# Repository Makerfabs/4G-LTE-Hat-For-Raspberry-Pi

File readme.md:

# 4G LTE Hat For Raspberry Pi

```c++
/*
Version:		V1.0
Author:			Vincent
Create Date:	2022/2/24
Note:
	
*/
```

[toc]

# Makerfabs

[Makerfabs home page](https://www.makerfabs.com/)

[Makerfabs Wiki](https://wiki.makerfabs.com/)

# 4G LTE Hat For Raspberry Pi
## Intruduce

Product Link ：[4G LTE Hat For Raspberry Pi(SIM7600X)]() 

Wiki Link : [4G LTE Hat For Raspberry Pi]() 

4G LTE Hat For Raspberry Pi integrated two types of the 4G LTE CAT4 module SIM7600A-H or SIM7600E-H, SIM7600A-H/SIM7600E-H is a complete multi-band LTE-FDD/LTE-TDD/HSPA+/UMTS/EDGE/GPRS/GSM module solution in LCC type which supports LTE CAT4 up to 150Mbps for downlink and 50Mbps for uplink data transfer, much faster and popular than 2G/3G.

It can be used as a wireless card with USB and raspberry PI connections. It can also be controlled through GPIO's hardware UART.

## Module Type

## Feature

- Supports dial-up, phone, SMS, TCP, UDP, DTMF, HTTP, FTP, and so on
- USB Type C port
- Control Via AT Commands
- Board USB supply voltage range: 4.8~5.5V, 5.0V Typical
- 3GPP E-UTRA Release 11
- IPEX Antenna, GSM/UMTS/LTE main antenna. UMTS/LTE auxiliary antenna. GNSS antenna
- SMS support
- Audio support
- Audio chip: NAU8810
- Level Shifter: TXS0108E

### Front:

### Back:

### Frequency bands

### Transfer Speed

## AT Command Explain

###  AT commands test

Refer to the official AT manual of SIM7600 for detailed return values.

```c++
    AT+CGMI    // Request manufacturer identification
    AT+CGMM    // Request model identification
    AT+CGSN    // Request product serial number identification
    AT+CSUB    // Request the module version and chip
    AT+CPIN?     // Request the state of the SIM card
    AT+CICCID    // Read ICCID from SIM card
    AT+CNUM      // Request the subscriber number
    AT+CNMP?     // Preferred mode selection
    AT+COPS?     // Check the current network operator
```

### Get the GNSS location

GPS signal acquisition speed depends on signal strength, please wait patiently in an open place.

```c++
    AT+CGPS=1      // Start GPS session 
    AT+CGPSINFO    // Get GPS fixed position information
    AT+CGPS=0      // Stop GPS session
```

### Send and receive SMS

Please consult the operator for the phone number of the SMS center. The number "+8613800755500" in Shenzhen was used in the test. 

```c++
    AT+CSCA="XXXXXX"       // Set the SMS service centre address
    AT+CMGF=1              // Select SMS message format
    AT+CMGS="xxxxxx"       // Send message to "xxxxxx"(the receiver number).
```

"AT+CMGS" sets the phone number of the receiver and returns ' >' . Send desired content, such as "Send Massage Test!".After editing a short message, send it in hexadecimal format 1A Send a message.

*The Arduino IDE cannot send hexadecimal,  you can use other software. In the example code, entering 1A or 1A will send 0x1A to the module.*

# Usage (Pi with USB)

## Equipment list

- Maduino Zero 4G (With GPS antenna and two 4G-GSM antennas)
- SIM card 

*Ensure that SIM7600 requirements are met and that the system can communicate with local carriers. We used China Mobile's 4G card for testing.*

- Connect all antennas
- Insert a SIM card
- Connect **USB for MCU** to Raspberry Pi USB

## Used as a 4G network adapter

### Hardware Check

- Log in to the root account and perform all subsequent operations as the root account.

```shell
sudo su
```

- Install the Minicom serial port tool.

```shell
apt-get install minicom
```

- To view the serial port device, AT command serial port: "/dev/ttyUSB2"

```shell
ls /dev/ttyUSB*
```

- Open the serial port with Minicom

```shell
minicom -D /dev/ttyUSB2
```

- Enter the AT command in minicom

```shell
# Forcibly set the Internet access to 4G
AT+CNMP=38
# Querying network Quality
AT+CSQ
# Query the network registry
AT+CREG?
# Querying Network Carrier Information
AT+COPS?
# Querying network band
AT+CPSI?
```

- \- Press Ctrl + A, then X to exit Minicom

At this point, the hardware and network connections between SIM7600CE and Raspberry Pi are normal. This case uses the 4G card of China Mobile. If you cannot use the other areas, please ask SIMCOM. 

### Driver Install

By default, Raspbian is installed with Qualcomm driver files for the wwan0 network port. For Raspberry Pi, you need to uninstall the driver first (otherwise it will conflict with the new driver), and then install the Simcom's driver for wwan0.

- Check system drivers

```shell
lsmod
```

- Uninstalling an existing driver

```shell
rmmod qmi_wwan
```

- Install the raspberry PI kernel header file
```shell
apt install raspberrypi-kernel-headers
```
- Download the official driver program provided by SIMCOM
```shell
wget https://www.waveshare.net/w/upload/0/00/SIM7600_NDIS.7z
```
- Install the decompression tool and decompress it
```shell
apt-get install p7zip-full
7z x SIM7600_NDIS.7z -r -o ./SIM7600_NDIS
```
- Go to the driver folder and compile

```shell
cd SIM7600_NDIS
make clean
make
ls
```

- Install the driver module file

```shell
insmod simcom_wwan.ko
```

- Check whether the installation is successful
```shell
lsmod
```

### Assign IP addresses

- In this case, the wwan0 network port is displayed

```shell
ifconfig -a
```
- However, no IP address is assigned to the network port. To assign an IP address, enable the network port first

```shell
ifconfig wwan0 up
```
- Then, through Minicom, enter the AT command to start dialing

```shell
minicom -D /dev/ttyUSB2
AT$QCRMCALL=1,1
```
- Finally, exit Minicom and assign IP

```shell
apt-get install udhcpc
udhcpc -i wwan0
```
- Run the Ping command to check whether the network adapter is connected

```shell
ping -I wwan0 www.baidu.com
```

# Usage (Pi with Uart)

We have connected the UART pin of SIM7600 to the UART of raspberry PI via GPIO.

SIM7600 can be connected using PySerial and other libraries. However, you need to set up the raspberry PI hardware UART, and it will use the Raspberry PI bluetooth.

The setting method is as follows:

```shell
#Set Pi uart
sudo raspi-config 

#Select interface options
#Select Serial Port
#Turn off serial login shell
#Open serial hardware
#Finish and reboot

#Install serial library
sudo apt-get update
sudo apt-get install pip
sudo pip install pyserial

python test.py
#Code is below
#Entry some at commands
```

**test.py**：

```python
import serial
from time import sleep
ser = serial.Serial("/dev/ttyS0", 115200)  # Open port with baud rate
while True:
    # Read cmd
    # You need press enter to receive new message
    # input() is block function
    cmd_input = input()
    if cmd_input != "":
        ser.write((cmd_input + "\r\n").encode('gbk'))

    # ser.write("AT".encode())  # It's error
    # ser.write("AT\r\n".encode('utf-8'))  # It's correct, contain "\r\n"
    sleep(1)

    # Receieve from SIM7600
    received_data = ser.read_all()  # read serial port
    print(received_data)  # print received bytes
    if received_data.decode() != "":
        print("Back:" + received_data.decode())  # print received data after decode

```

The AT-Command used are no different from those under Minicom.

**You need to manually add "\r\n", otherwise the module will just repeat the instructions you sent. **

# Usage （Windows）

- Connect one end of USB cable to USB interface of PC and the other end to USB_LTE interface of Maduino Zero 4G LTE.

- Open the device manager and you can see these COM ports.

- If the COM port is identified in the figure above, but an exclamation mark appears, it indicates that the driver is not installed.
- Driver is in "Maduino-Zero-4G-LTE\win_driver\SIM7600X-Driver.7z"
- Open Device Manager - > Other equipment - >“SimTech,Incorporated”- >  Update the driver - > Browse my computer to find driver files - > Select a path for saving the driver file based on the system- >The installation is complete.

- Install the driver for each exclamation point
- The network icon will then appear as a cellular network.

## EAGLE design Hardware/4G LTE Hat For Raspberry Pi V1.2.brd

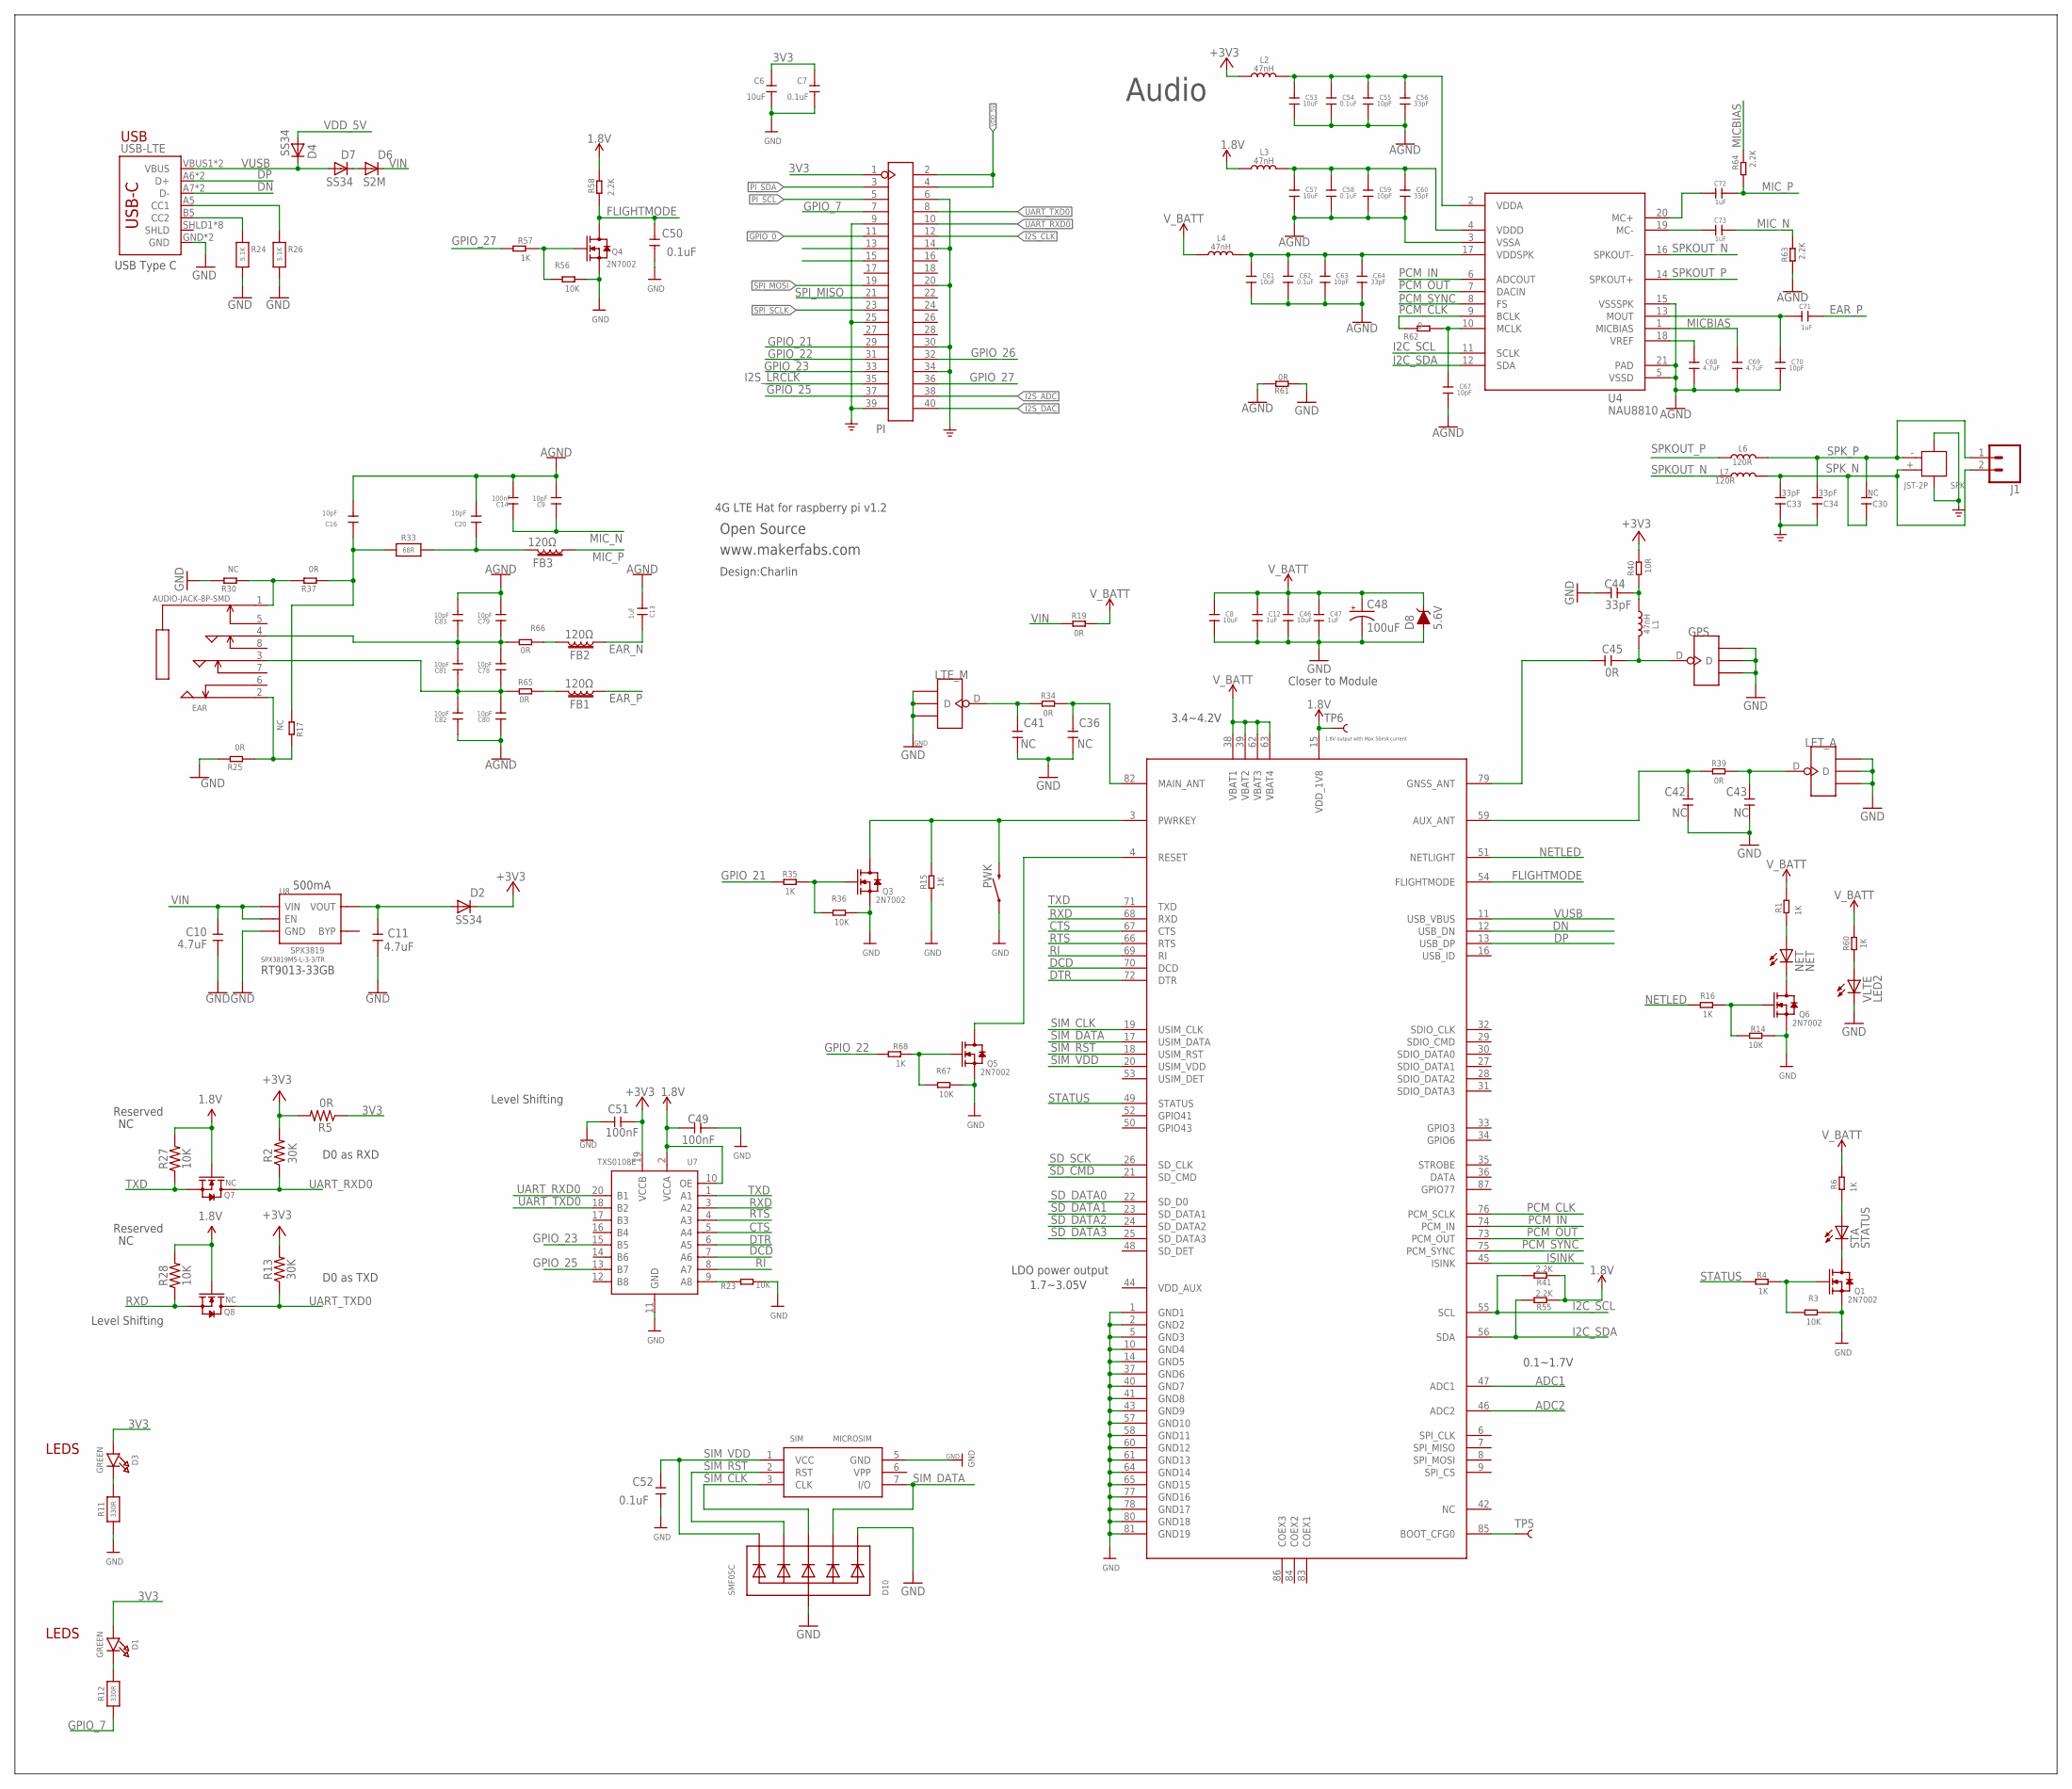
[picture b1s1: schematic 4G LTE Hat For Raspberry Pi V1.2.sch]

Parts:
C6: 10uF; DISCRETE_C0603
C7: 0.1uF; DISCRETE_C0603
C8, C46, C53, C57, C61: 10uF; C0603
C9, C16, C20, C55, C59, C63, C67, C70, C78, C79, C80, C81, C82, C83: 10pF; C0603
C10, C11, C68, C69: 4.7uF; C0603
C12, C13, C47, C71, C72, C73: 1uF; C0603
C14, C49, C51: 100nF; C0603
C30, C36, C41, C42, C43: NC; C0603
C33, C34, C44, C56, C60, C64: 33pF; C0603
C45: 0R; C0603
C48: 100uF; EIA3528
C50, C52, C54, C58, C62: 0.1uF; C0603
D1, D3: GREEN; CHIPLED_0805_NOOUTLINE
D2, D4, D7: SS34; DO-214AC
D6: S2M; DO-214AC
D8: 5.6V; SOD-323
D10: SMF05C; SOT363
EAR: AUDIO-JACK-8P-SMD; AUDIO8P-SMD-3.5-14.5X6.1X4.0MM
FB1, FB2, FB3: 120Ω; 0603
GPS: ANTENNA-U-FL; 4P-U-FL
J1: CONN_02LOCK; 1X02_LOCK
L1, L2, L3, L4: 47nH; L0603
L6, L7: 120R; L0603
LET_A: ANTENNA-U-FL; 4P-U-FL
LTE_M: ANTENNA-U-FL; 4P-U-FL
NET: NET; CHIP-LED0805
PI: HEADER-2X20P1; DIP-2X20-2.54MM
PWK: MOMENTARY-SWITCH-SPST-SMD-6.0X3.5MM; TACTILE_SWITCH_SMD_6.0X3.5MM
Q1, Q3, Q4, Q5, Q6: 2N7002; SOT23
Q7, Q8: NC; SOT23
R1, R4, R6, R15, R16, R35, R57, R60, R68: 1K; R0603
R2, R13: 30K; 0603
R3, R14, R23, R36, R56, R67: 10K; R0603
R5: 0R; 0603
R11, R12: 330R; 0603-NO
R17, R30: NC; R0603
R19, R25, R34, R37, R39, R61, R65, R66: 0R; R0603
R24, R26: 5.1K; 0603-NO
R27, R28: 10K; 0603
R33: 68R; 0603-NO
R40: 10R; R0603
R41, R55, R58, R63, R64: 2.2K; R0603
R62: 0; R0603
SIM: MICROSIM
SPK: JST-2P; HW2-SMD-2.0-90D
STA: STATUS; CHIP-LED0805
TP5, TP6: TEST-POINT3; PAD.03X.03
U4: NAU8810; QFN21-50P-400L400W
U6: SIM7600; SMD87-100P-3000L300W
U7: TXS0108E; TSSOP20-0.65-6.5X4.4MM
U8: SPX3819; SOT23-5
USB-LTE: USB_C5; USB-C-16P-5
VLTE: LED2; CHIP-LED0805

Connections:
1.8V: C49.2, L3.1, Q7.1 (G), Q8.1 (G), R27.2, R28.2, R41.1, R55.1, R58.2, TP6.P$1, U6.15 (VDD_1V8), U7.2 (VCCA), U7.10 (OE)
3V3: C6.2, C7.2, D1.A, D2.C, D3.A, L2.1, PI.1, R5.1
+3V3: C51.1, R2.2, R5.2, R13.2, R40.2, U7.19 (VCCB)
ADC1: U6.47 (ADC1)
ADC2: U6.46 (ADC2)
AGND: C9.1, C13.2, C14.1, C16.1, C20.1, C53.1, C54.1, C55.1, C56.1, C57.1, C58.1, C59.1, C60.1, C61.1, C62.1, C63.1, C64.1, C67.1, C68.1, C69.1, C70.1, C79.1, C80.2, C82.2, C83.1, R61.2, R63.1, U4.3 (VSSA), U4.5 (VSSD), U4.15 (VSSSPK), U4.21 (PAD)
CTS: U6.67 (CTS), U7.5 (A4)
DCD: U6.70 (DCD), U7.7 (A6)
DN: U6.12 (USB_DN), USB-LTE.A7 (D-), USB-LTE.B7 (D-)
DP: U6.13 (USB_DP), USB-LTE.A6 (D+), USB-LTE.B6 (D+)
DTR: U6.72 (DTR), U7.6 (A5)
EAR_N: C13.1, FB2.1
EAR_P: C71.1, FB1.1
FLIGHTMODE: C50.2, Q4.3 (D), R58.1, U6.54 (FLIGHTMODE)
GND: C6.1, C7.1, C8.1, C10.1, C11.1, C12.1, C33.2, C34.2, C36.1, C41.1, C42.1, C43.1, C44.2, C46.1, C47.1, C48.C (-), C49.1, C50.1, C51.2, C52.1, D8.A, D10.1 (C1), D10.2 (A), GPS.GND1, GPS.GND2, GPS.GND3, LET_A.GND1, LET_A.GND2, LET_A.GND3, LTE_M.GND1, LTE_M.GND2, LTE_M.GND3, PI.6, PI.9, PI.14, PI.20, PI.25, PI.30, PI.34, PI.39, PWK.1, Q1.2 (S), Q3.2 (S), Q4.2 (S), Q5.2 (S), Q6.2 (S), R3.1, R11.1, R14.1, R15.1, R23.1, R24.2, R25.2, R26.2, R30.2, R36.1, R56.1, R61.1, R67.1, SIM.5 (GND), SPK.3, SPK.4, U6.1 (GND1), U6.2 (GND2), U6.5 (GND3), U6.10 (GND4), U6.14 (GND5), U6.37 (GND6), U6.40 (GND7), U6.41 (GND8), U6.43 (GND9), U6.57 (GND10), U6.58 (GND11), U6.60 (GND12), U6.61 (GND13), U6.64 (GND14), U6.65 (GND15), U6.77 (GND16), U6.78 (GND17), U6.80 (GND18), U6.81 (GND19), U7.11 (GND), U8.2 (GND), USB-LTE.GND, USB-LTE.GND2 (GND), VLTE.C
GPIO_0: PI.11
GPIO_2: PI.13
GPIO_3: PI.15
GPIO_7: PI.7, R12.1
GPIO_21: PI.29, R35.2
GPIO_22: PI.31, R68.2
GPIO_23: PI.33, U7.15 (B5)
GPIO_25: PI.37, U7.13 (B7)
GPIO_26: PI.32
GPIO_27: PI.36, R57.2
I2C_SCL: R41.2, U4.11 (SCLK), U6.55 (SCL)
I2C_SDA: R55.2, U4.12 (SDA), U6.56 (SDA)
I2S_ADC: PI.38
I2S_CLK: PI.12
I2S_DAC: PI.40
I2S_LRCLK: PI.35
ISINK: U6.45 (ISINK)
MICBIAS: C69.2, R64.2, U4.1 (MICBIAS)
MIC_N: C9.2, C14.2, C73.1, R63.2
MIC_P: C72.1, FB3.1, R64.1
unnamed: C11.2, D2.A, U8.5 (VOUT)
unnamed: Q1.1 (G), R3.2, R4.1
unnamed: D1.C, R12.2
unnamed: R6.1, STA.A
unnamed: D3.C, R11.2
unnamed: Q1.3 (D), STA.C
unnamed: Q6.1 (G), R14.2, R16.1
unnamed: NET.A, R1.1
unnamed: NET.C, Q6.3 (D)
unnamed: TP5.P$1, U6.85 (BOOT_CFG0)
unnamed: D6.A, D7.C
unnamed: C16.2, R17.1, R33.1, R37.1
unnamed: C20.2, FB3.2, R33.2
unnamed: EAR.2, R17.2, R25.1
unnamed: R26.1, USB-LTE.A5 (CC1)
unnamed: R24.1, USB-LTE.B5 (CC2)
unnamed: EAR.1, R30.1, R37.2
unnamed: C78.1, C79.2, C81.1, C83.2, EAR.4, R66.1
unnamed: R23.2, U7.9 (A8)
unnamed: C36.2, R34.1, U6.82 (MAIN_ANT)
unnamed: C41.2, LTE_M.D, R34.2
unnamed: PWK.2, Q3.3 (D), R15.2, U6.3 (PWRKEY)
unnamed: Q3.1 (G), R35.1, R36.2
unnamed: R60.1, VLTE.A
unnamed: C53.2, C54.2, C55.2, C56.2, L2.2, U4.2 (VDDA)
unnamed: C70.2, C71.2, U4.13 (MOUT)
unnamed: C61.2, C62.2, C63.2, C64.2, L4.2, U4.17 (VDDSPK)
unnamed: C68.2, U4.18 (VREF)
unnamed: C57.2, C58.2, C59.2, C60.2, L3.2, U4.4 (VDDD)
unnamed: C73.2, U4.19 (MC-)
unnamed: C67.2, R62.1, U4.10 (MCLK)
unnamed: C72.2, U4.20 (MC+)
unnamed: FB1.2, R65.2
unnamed: FB2.2, R66.2
unnamed: C78.2, C80.1, C81.2, C82.1, EAR.3, R65.1
unnamed: Q5.3 (D), U6.4 (RESET)
unnamed: Q5.1 (G), R67.2, R68.1
unnamed: C43.2, LET_A.D, R39.2
unnamed: C44.1, L1.1, R40.1
unnamed: C42.2, R39.1, U6.59 (AUX_ANT)
unnamed: C45.2, U6.79 (GNSS_ANT)
unnamed: C45.1, GPS.D, L1.2
unnamed: Q4.1 (G), R56.2, R57.1
NETLED: R16.2, U6.51 (NETLIGHT)
PCM_CLK: R62.2, U4.9 (BCLK), U6.76 (PCM_SCLK)
PCM_IN: U4.6 (ADCOUT), U6.74 (PCM_IN)
PCM_OUT: U4.7 (DACIN), U6.73 (PCM_OUT)
PCM_SYNC: U4.8 (FS), U6.75 (PCM_SYNC)
PI_SCL: PI.5
PI_SDA: PI.3
RI: U6.69 (RI), U7.8 (A7)
RTS: U6.66 (RTS), U7.4 (A3)
RXD: Q8.2 (S), R28.1, U6.68 (RXD), U7.3 (A2)
SD_CMD: U6.21 (SD_CMD)
SD_DATA0: U6.22 (SD_D0)
SD_DATA1: U6.23 (SD_DATA1)
SD_DATA2: U6.24 (SD_DATA2)
SD_DATA3: U6.25 (SD_DATA3)
SD_SCK: U6.26 (SD_CLK)
SIM_CLK: D10.4 (C3), SIM.3 (CLK), U6.19 (USIM_CLK)
SIM_DATA: D10.3 (C2), SIM.7 (I/O), U6.17 (USIM_DATA)
SIM_RST: D10.5 (C4), SIM.2 (RST), U6.18 (USIM_RST)
SIM_VDD: C52.2, D10.6 (C5), SIM.1 (VCC), U6.20 (USIM_VDD)
SPI_MISO: PI.21
SPI_MOSI: PI.19
SPI_SCLK: PI.23
SPKOUT_N: L7.1, U4.16 (SPKOUT-)
SPKOUT_P: L6.1, U4.14 (SPKOUT+)
SPK_N: C30.2, C33.1, J1.2, L7.2, SPK.+ (1)
SPK_P: C30.1, C34.1, J1.1, L6.2, SPK.- (2)
STATUS: R4.2, U6.49 (STATUS)
TXD: Q7.2 (S), R27.1, U6.71 (TXD), U7.1 (A1)
UART_RXD0: PI.10, Q7.3 (D), R2.1, U7.20 (B1)
UART_TXD0: PI.8, Q8.3 (D), R13.1, U7.18 (B2)
VDD_5V: D4.A, PI.2, PI.4
VIN: C10.2, D6.C, R19.2, U8.1 (VIN), U8.3 (EN)
VUSB: D4.C, D7.A, U6.11 (USB_VBUS), USB-LTE.VBUS1 (VBUS), USB-LTE.VBUS2 (VBUS)
V_BATT: C8.2, C12.2, C46.2, C47.2, C48.A (+), D8.C, L4.1, R1.2, R6.2, R19.1, R60.2, U6.38 (VBAT1), U6.39 (VBAT2), U6.62 (VBAT3), U6.63 (VBAT4)

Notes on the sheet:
4G LTE Hat for raspberry pi v1.2
LEDS
www.makerfabs.com
Design:Charlin
Open Source
Closer to Module
1.8V output with Max 50mA current
LDO power output
3.4~4.2V
0.1~1.7V
1.7~3.05V
Level Shifting
Reserved
USB
USB Type C
D0 as RXD
D0 as TXD
Audio
500mA
SPX3819M5-L-3-3/TR
RT9013-33GB

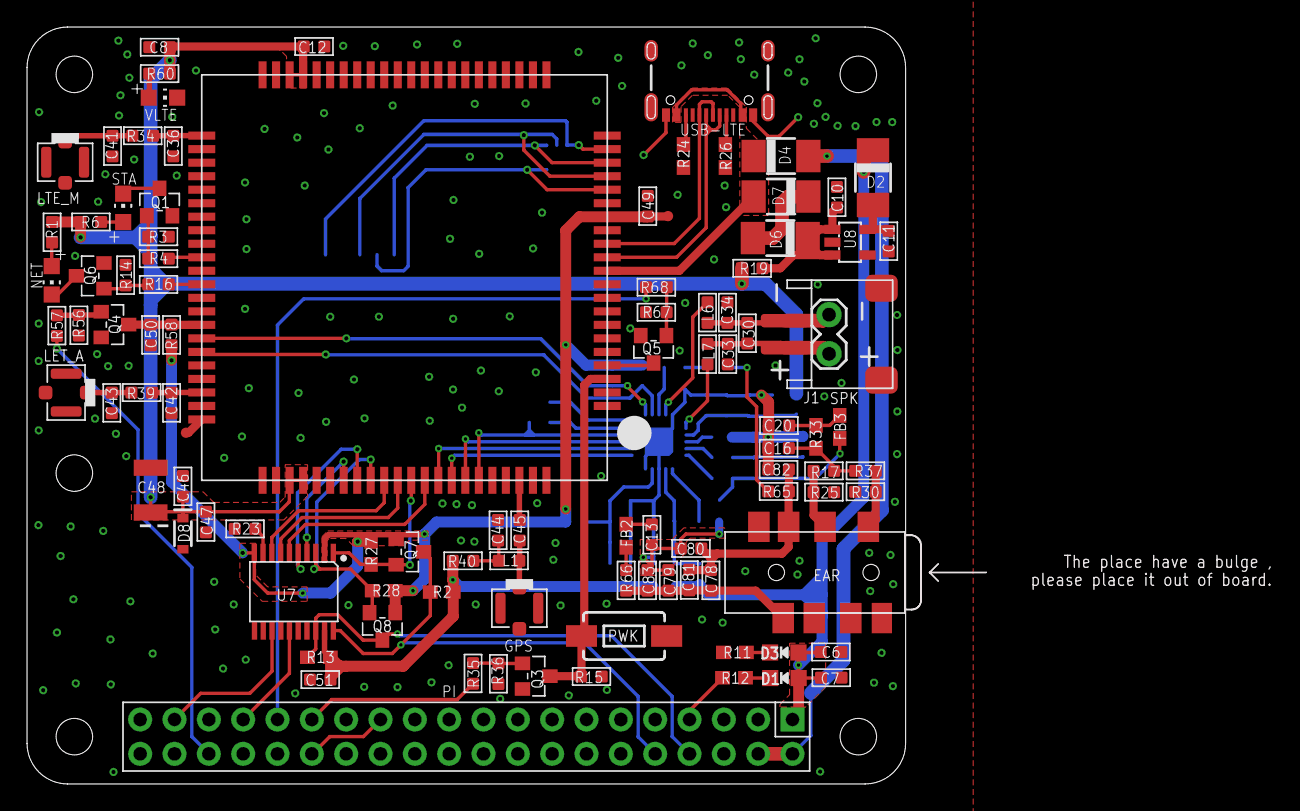
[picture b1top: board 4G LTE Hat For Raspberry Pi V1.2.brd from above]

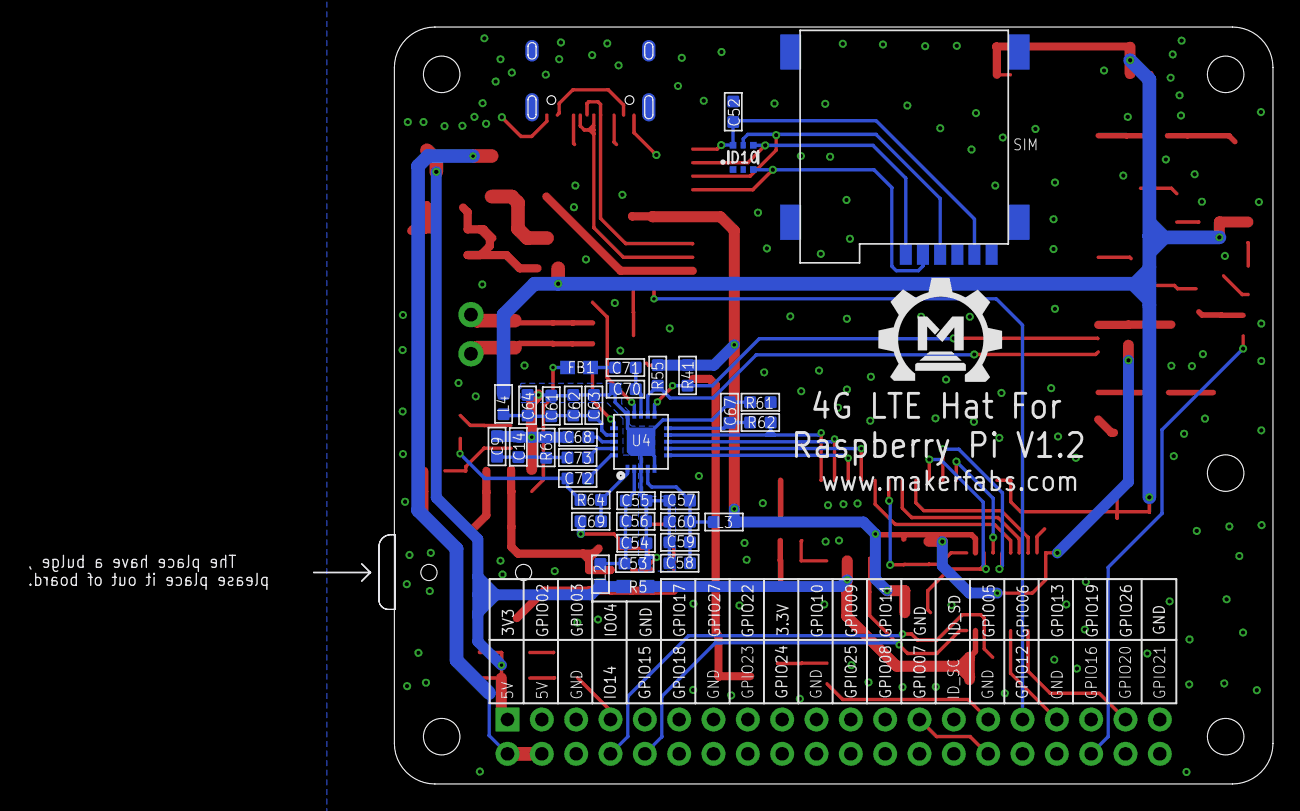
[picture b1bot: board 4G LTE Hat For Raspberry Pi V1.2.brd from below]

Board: 2 copper layers, 71.0 x 56.0 mm, 138 parts (37 on the bottom side), 91 nets.

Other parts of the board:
U$1: MAKERFABS_0.3

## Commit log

2022-02-24 Edit readme
2022-03-02 Hardware
    v1.0
2026-04-22 Add hardware V1.2

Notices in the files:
parts and their libraries:
microbuilder: This work is placed in the public domain, and may be freely used for commercial and non-commercial work with the following conditions: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
SparkFun-Capacitors: Licensing: Creative Commons ShareAlike 4.0 International - https://creativecommons.org/licenses/by-sa/4.0
